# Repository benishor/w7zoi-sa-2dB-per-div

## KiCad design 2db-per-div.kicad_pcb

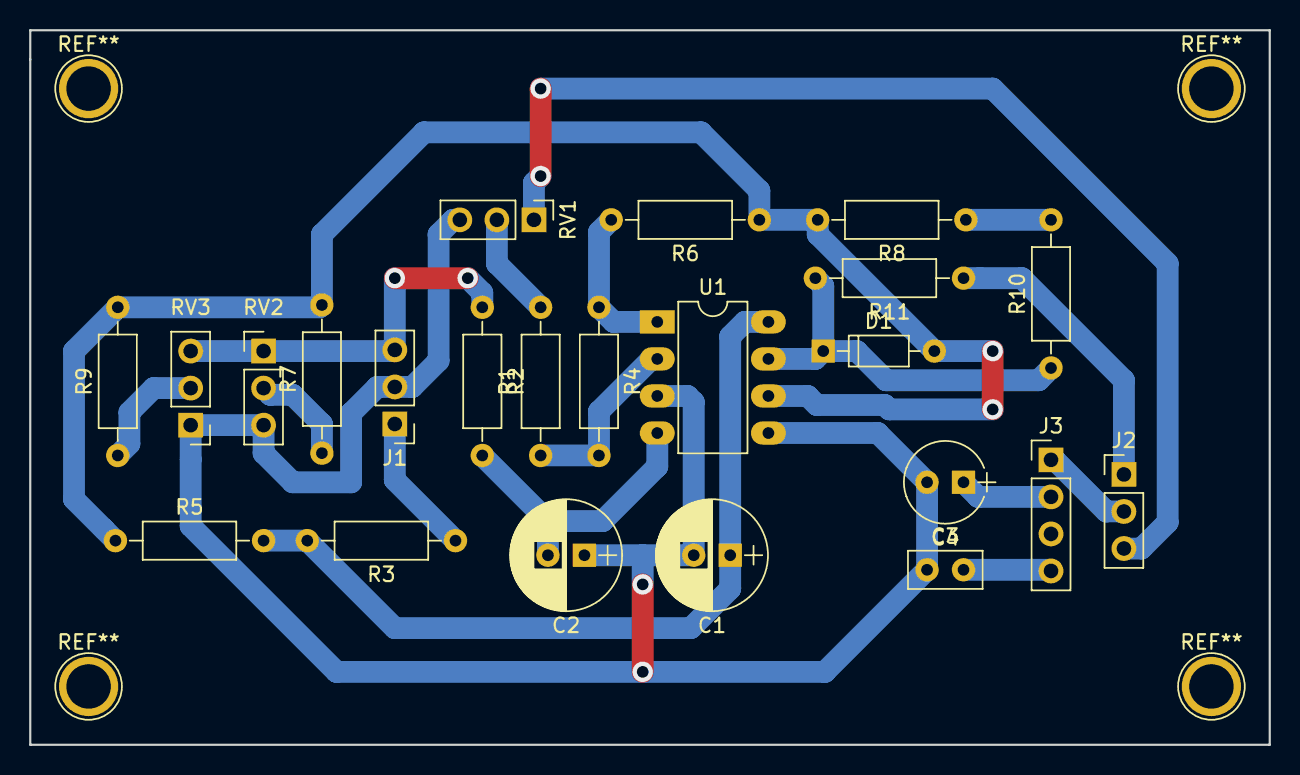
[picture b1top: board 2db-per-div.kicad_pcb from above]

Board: 2 copper layers, 85.0 x 49.0 mm, 23 parts (0 on the bottom side), 18 nets.

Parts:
C1, C2: 100u; CP_Radial_D7.5mm_P2.50mm
C3: 0.1u; C_Disc_D5.0mm_W2.5mm_P2.50mm
C4: 3.3u; CP_Radial_Tantal_D5.5mm_P2.50mm
D1: 1N4152; D_DO-35_SOD27_P7.62mm_Horizontal
J1: POWER; Pin_Header_Straight_1x03_Pitch2.54mm
J2: RANGE_SWITCH; Pin_Header_Straight_1x03_Pitch2.54mm
J3: VIDEO_FILTER; Pin_Header_Straight_1x04_Pitch2.54mm
R1, R5, R7, R8: 20K; R_Axial_DIN0207_L6.3mm_D2.5mm_P10.16mm_Horizontal
R2, R3: 43; R_Axial_DIN0207_L6.3mm_D2.5mm_P10.16mm_Horizontal
R4: 40K; R_Axial_DIN0207_L6.3mm_D2.5mm_P10.16mm_Horizontal
R6: 10K; R_Axial_DIN0207_L6.3mm_D2.5mm_P10.16mm_Horizontal
R9: 249K; R_Axial_DIN0207_L6.3mm_D2.5mm_P10.16mm_Horizontal
R10: 4.99K; R_Axial_DIN0207_L6.3mm_D2.5mm_P10.16mm_Horizontal
R11: 1K; R_Axial_DIN0207_L6.3mm_D2.5mm_P10.16mm_Horizontal
RV1: 5K; Pin_Header_Straight_1x03_Pitch2.54mm
RV2, RV3: 10K; Pin_Header_Straight_1x03_Pitch2.54mm
U1: LM1458; DIP-8_W7.62mm_LongPads

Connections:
+15V: J1.1, R3.1
-15V: J1.3, R2.1, RV2.1, RV3.3
GND: C1.2, C2.1, C3.1, C4.2, J1.2, RV1.3, RV2.3, RV3.1, U1.3, U1.5
INPUT: R1.2, RV1.2
LOG_AMP_OUTPUT: J2.3, RV1.1
unnamed: C1.1, R3.2, R5.2, U1.8
unnamed: C2.2, R2.2, U1.4
unnamed: C3.2, J3.4
unnamed: C4.1, J3.2
unnamed: D1.1, R10.1, R11.2, U1.7
unnamed: D1.2, R5.1, R6.1, R7.2, R8.2, R9.2, U1.6
unnamed: R1.1, R4.2, U1.2
unnamed: R4.1, R6.2, U1.1
unnamed: R7.1, RV2.2
unnamed: R9.1, RV3.2
unnamed: R8.1, R10.2
OUTPUT: J2.2, J3.1
OUTPUT_2dB_PER_DIV: J2.1, R11.1

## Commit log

2017-04-15 Initial import
